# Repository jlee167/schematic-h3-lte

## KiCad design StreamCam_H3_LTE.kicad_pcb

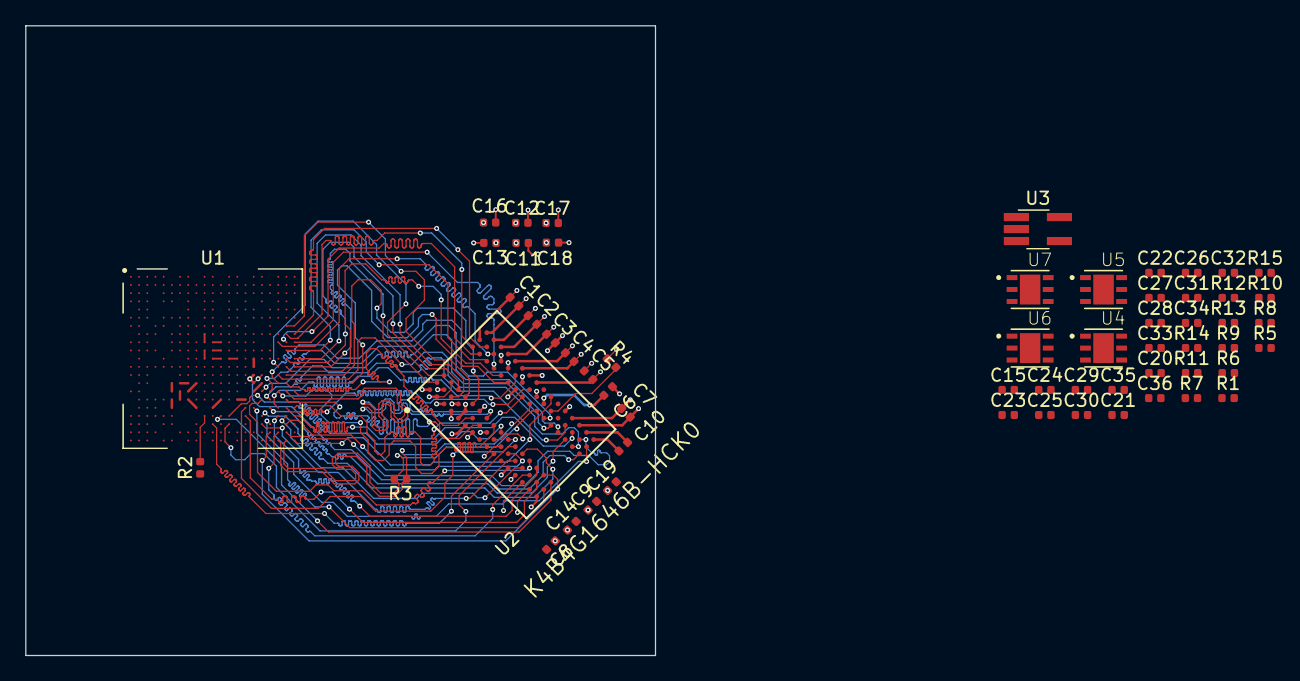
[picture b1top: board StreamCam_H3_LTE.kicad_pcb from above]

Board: 4 copper layers, 50.0 x 50.0 mm, 58 parts (0 on the bottom side), 71 nets.

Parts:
C1, C2, C3, C4, C5, C6, C7, C8, C9, C10, C11, C12, C13, C14, C16, C17, C18, C19: C_Small; C_0402_1005Metric
C15, C29, C30, C31, C32: 100nF; C_0402_1005Metric
C20, C21, C22, C23, C25, C27, C34, C36: 10uF; C_0402_1005Metric
C24, C26, C35: 22pF; C_0402_1005Metric
C28: 1uF; C_0402_1005Metric
C33: 4.7uF; C_0402_1005Metric
R1, R9, R13: 0; R_0402_1005Metric
R2, R4: 240R/1%; R_0402_1005Metric
R3: R_Small_US; R_0402_1005Metric
R5: 1.6k; R_0402_1005Metric
R6, R8, R15: 1k; R_0402_1005Metric
R7: 2k; R_0402_1005Metric
R10: 100k; R_0402_1005Metric
R11: 47k; R_0402_1005Metric
R12: 10k; R_0402_1005Metric
R14: 1.4k; R_0402_1005Metric
U1: Allwinner_H3; H3_21x21_14.0x14.0mm
U2: K4B4G1646B-HCK0; Samsung-96FBGA-0-0-IPC_A_
U3: rt8059; TSOT-23-5_HandSoldering
U4, U6, U7: LD39200PUR; LD39200PU33R
U5: LD39200PU33R

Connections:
+1V2: C35.1, C36.1, R14.1, U1.H10, U1.J10, U1.J11, U1.J12, U1.K10, U1.K11, U1.K12, U1.L10, U1.L11, U1.L12, U1.L13, U1.L14, U7.1, U7.2
+3V3: C15.1, C22.1, C29.1, C32.1, C34.1, R10.1, R11.1, R12.1, U1.G11, U1.G13, U1.G14, U1.G15, U1.H13, U1.H14, U1.J6, U1.J14, U1.J15, U1.K6, U5.1, U5.2, U7.5, U7.6
+BATT: C20.1, C21.1, C25.1, U4.5, U4.6, U5.5, U5.6, U6.5, U6.6
/Sheet6067B01D/SA0: U1.T17, U2.N3
/Sheet6067B01D/SA1: U1.U18, U2.P7
/Sheet6067B01D/SA2: U1.V19, U2.P3
/Sheet6067B01D/SA3: U1.V20, U2.N2
/Sheet6067B01D/SA4: U1.V21, U2.P8
/Sheet6067B01D/SA5: U1.Y19, U2.P2
/Sheet6067B01D/SA6: U1.Y20, U2.R8
/Sheet6067B01D/SA7: U1.V15, U2.R2
/Sheet6067B01D/SA8: U1.W18, U2.T8
/Sheet6067B01D/SA9: U1.Y18, U2.R3
/Sheet6067B01D/SA10: U1.P19, U2.L7
/Sheet6067B01D/SA11: U1.N19, U2.R7
/Sheet6067B01D/SA12: U1.R18, U2.N7
/Sheet6067B01D/SA13: U1.V12, U2.T3
/Sheet6067B01D/SA14: U1.N17, U2.T7
/Sheet6067B01D/SA15: U1.R17, U2.M7
/Sheet6067B01D/SBA0: U1.W17, U2.M2
/Sheet6067B01D/SBA1: U1.T18, U2.N8
/Sheet6067B01D/SBA2: U1.V17, U2.M3
/Sheet6067B01D/SCAS: U1.U15, U2.K3
/Sheet6067B01D/SCKE0: U1.AA21, U2.K9
/Sheet6067B01D/SCS0: U1.W20, U2.L2
/Sheet6067B01D/SDQ0: U1.N20, U2.E3
/Sheet6067B01D/SDQ1: U1.P21, U2.F7
/Sheet6067B01D/SDQ2: U1.P20, U2.F2
/Sheet6067B01D/SDQ3: U1.U21, U2.H7
/Sheet6067B01D/SDQ4: U1.R19, U2.H3
/Sheet6067B01D/SDQ5: U1.T20, U2.G2
/Sheet6067B01D/SDQ6: U1.U19, U2.F8
/Sheet6067B01D/SDQ7: U1.U20, U2.H8
/Sheet6067B01D/SDQ8: U1.J19, U2.C8
/Sheet6067B01D/SDQ9: U1.H20, U2.A7
/Sheet6067B01D/SDQ10: U1.H21, U2.B8
/Sheet6067B01D/SDQ11: U1.J21, U2.D7
/Sheet6067B01D/SDQ12: U1.L20, U2.C3
/Sheet6067B01D/SDQ13: U1.L21, U2.C2
/Sheet6067B01D/SDQ14: U1.M21, U2.A2
/Sheet6067B01D/SDQ15: U1.M19, U2.A3
/Sheet6067B01D/SDQM0: U1.M20, U2.E7
/Sheet6067B01D/SDQM1: U1.G20, U2.D3
/Sheet6067B01D/SDQS0N: U1.R21, U2.G3
/Sheet6067B01D/SDQS0P: U1.R20, U2.F3
/Sheet6067B01D/SDQS1N: U1.J20, U2.B7
/Sheet6067B01D/SDQS1P: U1.K20, U2.C7
/Sheet6067B01D/SODT0: U1.W11, U2.K1
/Sheet6067B01D/SRAS: U1.V13, U2.J3
/Sheet6067B01D/SRST: U1.U16, U2.T2
/Sheet6067B01D/SWE: U1.W13, U2.L3
/Sheet6067B01D/sck_N: R3.2, U1.AA20, U2.K7
/Sheet6067B01D/sck_P: R3.1, U1.AA19, U2.J7
/VDD_CPUFB: C24.1, R5.1, U1.T10, U4.2
/vdd_cpus: C28.1, C30.1, C33.1, U1.J7, U1.J8, U1.M4
GND: C15.2, C20.2, C21.2, C22.2, C23.2, C25.2, C27.2, C28.2, C29.2, C30.2, C31.2, C32.2, C33.2, C34.2, C36.2, R1.2, R6.2, R8.2, R13.2, R15.2, U1.A21, U1.AA1, U1.B21, U1.G8, U1.H8, U1.H12, U1.H15, U1.J9, U1.J13, U1.J16, U1.K7, U1.K8, U1.K9, U1.K13, U1.K14, U1.K15, U1.K16, U1.L8, U1.L9, U1.L15, U1.M5, U1.M7, U1.M8, U1.M9, U1.M10, U1.M11, U1.M12, U1.M13, U1.M14, U1.M15, U1.N7, U1.N9, U1.N10, U1.N11, U1.N12, U1.N13, U1.N14, U1.N15, U1.P10, U1.P11, U1.P12, U1.P13, U1.P14, U1.P15, U1.R9, U1.R10, U1.R11, U1.R12, U1.R13, U1.R14, U1.T11, U4.3, U4.7, U5.3, U5.7, U6.3, U6.7, U7.3, U7.7
GND1: C1.2, C2.2, C3.2, C4.2, C5.2, C6.2, C7.2, C8.2, C9.2, C10.2, C11.2, C12.2, C13.2, C14.2, C16.2, C17.2, C18.2, C19.2, R2.1, R4.1, U2.A9, U2.B1, U2.B3, U2.B9, U2.D1, U2.D8, U2.E1, U2.E2, U2.E8, U2.F9, U2.G1, U2.G8, U2.G9, U2.J2, U2.J8, U2.M1, U2.M9, U2.P1, U2.P9, U2.T1, U2.T9
GNDA: R1.1, U1.U3
unnamed: C24.2, R5.2, R6.1
unnamed: C26.2, R7.2, R8.1
unnamed: C31.1, R9.2, U1.G9
unnamed: C35.2, R14.2, R15.1
unnamed: R2.2, U1.V10
unnamed: R4.2, U2.L8
unnamed: R10.2, U1.AA5
unnamed: R11.2, U1.AA6
unnamed: R12.2, U1.W6
unnamed: R13.1, U1.T9
VDD: C23.1, U1.N8, U1.P6, U1.P7, U1.P8, U1.P9, U1.R6, U1.R7, U1.R8, U1.T6, U1.T7, U1.T8, U1.U6, U1.U9, U4.1
VDDA: R9.1, U1.V3
VMEM: C1.1, C2.1, C3.1, C4.1, C5.1, C6.1, C7.1, C8.1, C9.1, C10.1, C11.1, C12.1, C13.1, C14.1, C16.1, C17.1, C18.1, C19.1, C26.1, C27.1, R7.1, U1.L16, U1.M16, U1.N16, U1.P16, U1.P17, U1.R16, U1.T12, U1.T13, U1.T14, U1.T15, U1.U11, U2.A1, U2.A8, U2.B2, U2.C1, U2.C9, U2.D2, U2.D9, U2.E9, U2.F1, U2.G7, U2.H2, U2.H9, U2.K2, U2.K8, U2.N1, U2.N9, U2.R1, U2.R9, U6.1, U6.2

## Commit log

2021-04-28 DDR3 Routing Done
